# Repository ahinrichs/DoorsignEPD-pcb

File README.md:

## DoorsignEPD-pcb

ESP-WROOM-32 breakout board to connect it to a Waveshare E-Ink display. 

Inspired by article [Ausdauernde Infotafel](https://ct.de/yrzv) from German
computer magazine [c't](https://ct.de). Example arduino and server software can
be found [here](https://github.com/jamct/DoorsignEPD/).

Input voltage is connected to a voltage regulator jack and directly to
Pin6/IO34/ADC6 for monitoring. Hence input voltage must be below 3.6V.  I use
2xAA together with a step up regulator. Additionally I connected a pad for
Pin8/IO32/ADC4/TOUCH9. Haven't used it yet. Maybe for a touch wakeup or status
LED.

Display connector pin assignment is identical to the Waveshare hat connector.

Rev A2 PCB can be ordered e.g. via aisler.net: https://aisler.net/p/HSIWEKKI

Components needed in addition to PCB:

* Of course an ESP-WROOM-32 (or footprint compatible)
* Waveshare E-Ink display
* 3.3V voltage regulator or other 3.3V source
* Battery + holder of your choice
* 2x ~10kΩ pullup resistors R1+R2
* 2x tactile switch (included in aisler precious parts)
* 1x JST-PH 8 connector header+housing (included in aisler precious parts)
* 1x JST-PH 2 connector header+housing (included in aisler precious parts)
* 10-15 JST-PH terminals (included in aisler precious parts)
* Crimp tool for JST-PH connectors
* 3.3V capable USB-TTL adapter for programming

### Programming

This a minimalistic board to save power. No USB included. So you need an
USB-TTL adapter that is capable of doing 3.3V. [This one](https://www.amazon.de/WINGONEER-CP2104-seriell-Konverter-TTL-kompatibel/dp/B01CYBHM26) works for me under
Linux.

To upload an arduino sketch/flash firmware:

1. Connect the USB-Adapter GND/RX/TX to the board. Most adapters need RX board/TX adapter and TX board/RX adapter. If that doesn't work try RX/RX+TX/TX. To check press the Reset button. The serial monitor must show the ESP33 boot log.
2. Press and hold the Boot(loader) button, shortly press the Reset button, then release the Boot button. Log should show the ESP32 entering bootloader mode.
3. Now stop any serial monitor (Arduino IDE does this automatically)
4. Upload the sketch and wait until completion
5. Again press the Reset button
6. Restart serial monitor (Arduino IDE does this automatically)

### Assembled board

### Changelog

#### Rev A2 (minor)

* Trace width power supply + GND
* Via min size 0.65mm (=drill + 0.25mm)

#### Rev A1

* Initial revision

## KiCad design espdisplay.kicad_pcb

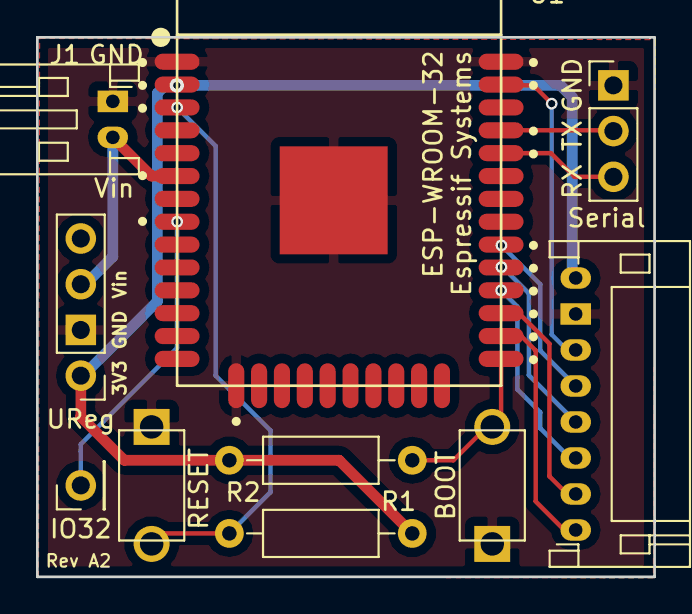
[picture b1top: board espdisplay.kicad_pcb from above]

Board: 2 copper layers, 34.3 x 30.0 mm, 10 parts (0 on the bottom side), 14 nets.

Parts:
J1: PWR; JST_PH_S2B-PH-K_02x2.00mm_Angled
J2: UReg; Pin_UReg_1x04_Pitch2.54mm
J3: DOut; JST_PH_S8B-PH-K_08x2.00mm_Angled
J4: Serial; Pin_Header_Straight_1x03_Pitch2.54mm
J5: IO32; Pin_Header_Straight_1x01_Pitch2.54mm
R1, R2: 10k; R_Axial_DIN0207_L6.3mm_D2.5mm_P10.16mm_Horizontal
SW1: RESET; SW_Tactile_SPST_NO_6mmx3.5mm
SW2: BOOT; SW_Tactile_SPST_NO_6mmx3.5mm
U1: ESP-WROOM-32

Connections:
+3V3: J2.1, J3.8, R1.1, R2.1, U1.2
/BUSY: J3.1, U1.26
/CLK: J3.5, U1.30
/CS: J3.4, U1.29
/DC: J3.3, U1.28
/DIN: J3.6, U1.37
/IO32: J5.1, U1.8
/RST: J3.2, U1.27
/Vin: J1.2, J2.3, U1.6
GND: J1.1, J2.2, J3.7, J4.1, SW1.1, SW2.1, U1.1, U1.15, U1.38, U1.39
unnamed: J4.2, U1.35
unnamed: J4.3, U1.34
unnamed: R1.2, SW1.2, U1.3
unnamed: R2.2, SW2.2, U1.25

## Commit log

2018-04-12 Init
2018-04-12 Use global labels
2018-04-13 Revert "Use global labels"
    This reverts commit 96ed9b38a919df69e8aa619b2320596f596cf7ae.
2018-04-16 Minor
2018-04-27 Vias 0.65mm
2018-04-27 Trace width
2018-04-27 Trace cleanup
2018-04-27 Readme
2018-04-27 Via min size
2018-04-27 cleanup and pwr trace width
2018-04-27 Rev A2
2018-04-27 "merge" rev.a2
2018-04-27 readme: programming howto
2018-04-27 readme: fix missing link

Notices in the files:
espdisplay.kicad_pcb:
Licensed under the TAPR Open Hardware License (www.tapr.org/OHL)
(c) 2018 Axel Hinrichs
